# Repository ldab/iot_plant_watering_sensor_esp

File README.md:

# iot_plant_watering_sensor_esp32
Connected, IoT, WiFi capacitance plant watering sensor based on ESP32

 ## TODO

- [ ] Better battery polarity indication and reverse polarity protection;
- [ ] Fix R16 - R19 Silk
- [ ] R15 is leaking 200uA
- [ ] Check if `esp_light_sleep_start()` improves current vs `delay(x)`
- [ ] Inspect connection time if BSSID is saved vs Saving time
- [ ] FOTA
- [ ] Error reporting and callbacks, i.e FFAT, ADC read, etc..

## VOID

"Lorem ipsum dolor sit amet, consectetur adipiscing elit, sed do eiusmod tempor incididunt ut labore et dolore magna aliqua. Ut enim ad minim veniam, quis nostrud exercitation ullamco laboris nisi ut aliquip ex ea commodo consequat. Duis aute irure dolor in reprehenderit in voluptate velit esse cillum dolore eu fugiat nulla pariatur. Excepteur sint occaecat cupidatat non proident, sunt in culpa qui officia deserunt mollit anim id est laborum."

## Working modes and button

* The device will check the moisture 2x a day, at 8am and 6pm;
* On Sundays it will connect to the internet and check time, etc;
* Insert the battery **WATCH THE POLAITY**;
* Press and hold the `config` button;
  * keep it pressed, it will connect to the internet, get the time and date and calibrate the sensor;
  * if everything goes well, it buzzes like this [link for audio]()
* If the battery voltage is lower than 2V, an `email` will be sent and it buzzes like this [link for audio](./ringtones/urgent.mid)
* If the soil is drier than the setpoint, an `email` will be sent and it buzzes like this [link for audio]()
* If a new level of alarm is nedded, press and hold the config button until a buzz like this [link for audio]() is heard;

## Component selection and Capacitive probe

* We need the most range on the voltage across the probe as possible, considering

**`Vc = 3 * (1 - e(-t / (R * C)))`**

* Varying R from 100 to 15000 Ω @ 1MHz:

[Wolfram Alpha - R Graph](https://www.wolframalpha.com/input/?i=plot+3+*+%281+-+e%5E%28-500*10%5E-9%2F%28R*50*10%5E-12%29%29%29+-+3+*+%281+-+e%5E%28-500*10%5E-9%2F%28R*200*10%5E-12%29%29%29%2C+R%3D+100+to+15000)

* From the graph below we go with 5KΩ, the capacitance of the probe varies from 50pF to 200pF:

[Wolfram Alpha - C Graph](https://www.wolframalpha.com/input/?i=plot+3+*+%281+-+e%5E%28-500*10%5E-9%2F%285000*C%29%29%29%2C+C%3D50*10%5E-12+to+200*10%5E-12)

* With a voltage range of 2.6 to 1.2 **~1.4V**.

## Capacitive sensor measurement

* When in the air, the sensor measures ~2.67V @ 1666(adc)

.BMP)

* And below 1000 (adc) ~1.8V when wet soil/water

.BMP)

## PSEUDO-CODE

```
main()
{ 
  turn radio OFF;
  config pins;

  read RTC();

  if( dateIsNotSet )    // probably first time
  {
    beep 2x;
    connect to the internet;
    set date;
    config RTC;
  }

  read moisture;

  if( alarmIsNotActive ) // wake from button
  {
    beep 5x;
    set new moisture level;
    clear alarm flag;    // aka sleep
  }
  else
  {
    if( moisture < threshould)
    {
      connect to the internet;
      send email/MQTT;
      turn radio OFF;

      while( times )
      {
        chrip
      }

      wake 
      clear alarm flag;    // aka sleep
    }
    else
    {
      clear alarm flag;    // aka sleep
    }
  }

  printf should never get here
} 
```

## Power Profile

* The DHCP negotiation and IP assignment can take a long time depending on the router, the below example is from a fairly long avg 90mA@2.8V for 3 s -> Includes ADC reading and MQTT publish

* When not connecting to WiFi, it is a lot faster:

* And during sleep 6uA@2.8V maninly due to the battery ADC (VCC/1MOhm =~ 3uA) and Boost disabled, ~1uA

* Primary battery CR-2 drops a bit during active, 280mv:

## Calibrating ADC for ESP32

* ADC on ESP32 has been reported being innacurate, therefore one can use ```adc2_vref_to_gpio( GPIO_NUM_25 );``` to route `Vref` to `GPIO_NUM_25` that can be measured over `ESP32 pin 10` in order to calibrate during ADC measurement.
* Calling for `esp_adc_cal_characterize(ADC_UNIT_1, ADC_ATTEN_DB_6, ADC_WIDTH_BIT_11, Vref, adc_chars);`

https://docs.espressif.com/projects/esp-idf/zh_CN/latest/esp32/api-reference/peripherals/adc.html

## FFat and time

```
  [641] IP address: 192.168.0.22
  Contacting Time Server
  [854] Now is : 2020-11-27T16:37:33
  Writing file: /hello.txt
  File written
  [1030] DONE writing, took: 176ms
  Reading file: /hello.txt
  Read from file: 2020-11-27T16:37:33
  [1093] DONE reading, took: 5ms
```

## Schematic

## PCB

## Enclosure

## Known Limitations

* 

## Credits

Github Shields and Badges created with [Shields.io](https://github.com/badges/shields/)

Inspired by [chirp! - the plant watering alarm](https://wemakethings.net/chirp/)

ESP32 Pin definition and overview https://randomnerdtutorials.com/esp32-pinout-reference-gpios/

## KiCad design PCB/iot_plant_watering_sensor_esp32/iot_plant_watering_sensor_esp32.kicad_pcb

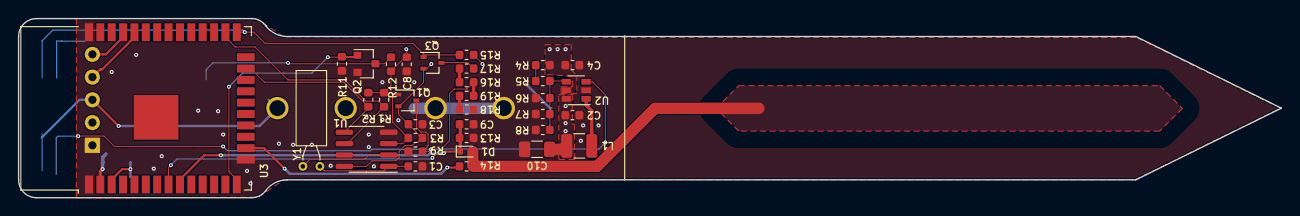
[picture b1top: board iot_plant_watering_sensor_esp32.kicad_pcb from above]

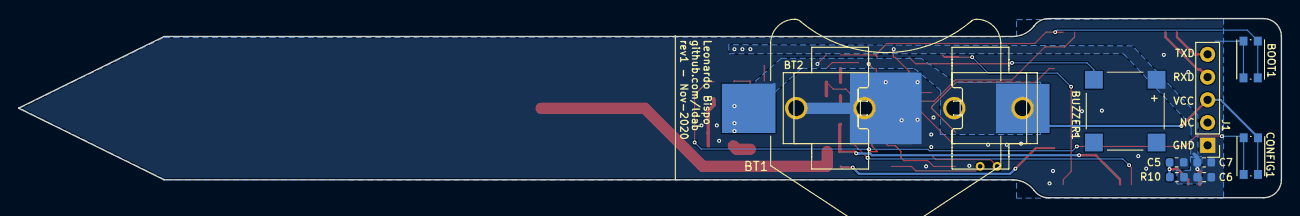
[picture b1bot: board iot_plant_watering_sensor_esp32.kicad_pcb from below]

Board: 2 copper layers, 141.0 x 20.0 mm, 44 parts (10 on the bottom side), 25 nets.

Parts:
BOOT1: SW_Push_KMR2; SW_Push_1P1T_NO_CK_KMR2
BT1: LIR2450; BatteryHolder_Keystone_3008_1x2450
BT2: CR2; 2915_CR2
BUZZER1: FUET-8530H-3.6V; PUIAudio_SMT_0825_S_4_R
C1: 25p; C_0603_1608Metric
C2, C4, C7: 10u; C_0603_1608Metric
C3, C5, C6: 100n; C_0603_1608Metric
C8, C9: 1u; C_0603_1608Metric
C10: 100u; C_1206_3216Metric
CONFIG1: SW_Push_KMR2; SW_Push_1P1T_NO_CK_KMR2
D1: RB751S40T1G; D_SOD-523
J1: Conn_01x05; PinHeader_1x05_P2.54mm_Snuggly
L1: 4.7u; L_1210_3225Metric
Q1, Q3: BSS84W-7-F; SOT-323_SC-70
Q2: 2N7002P,215; SOT-23
R1, R2, R3, R9, R10, R11, R14, R15: 10K; R_0603_1608Metric
R4, R5, R6, R7, R8, R13, R16, R17, R18, R19: 510K; R_0603_1608Metric
R12: 1K; R_0603_1608Metric
U1: PCF8563T; SOIC-8_3.9x4.9mm_P1.27mm
U2: FP6714; SOT-23-6
U3: ESP32-WROOM-32
Y1: 32.768 kHz; Crystal_C38-LF_D3.0mm_L8.0mm_Horizontal

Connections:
+3V3: BUZZER1.1, C4.1, C6.1, C7.1, C8.1, R1.2, R2.2, R4.1, R10.2, R12.1, U2.5, U3.2
+BATT: BT1.1, BT2.1, C2.1, C3.1, C10.1, CONFIG1.2, J1.3, L1.1, Q1.2, Q3.2, R3.2, R15.2, U1.8, U2.6
/C_SENSOR+: D1.2, R14.2
BATT_ADC: R17.2, R18.1, U3.8
BOOT: BOOT1.2, Q3.1, R15.1, U3.25
BUZZER: Q2.1, R11.2, U3.14
C_SENSE: C9.1, D1.1, R13.1, U3.9
FB: R5.2, R6.1, R7.1, R8.1, U2.4
GND: BOOT1.1, BT1.2, BT2.2, C1.2, C2.2, C3.2, C4.2, C5.2, C6.2, C7.2, C8.2, C9.2, C10.2, J1.1, Q2.2, R6.2, R7.2, R8.2, R9.1, R11.1, R13.2, R19.2, U1.4, U2.2, U3.1, U3.15, U3.38
LDO_EN: CONFIG1.1, Q1.3, R9.2, U2.3
unnamed: BUZZER1.2, Q2.3, R12.2
unnamed: C1.1, U1.1, Y1.1
unnamed: C5.1, R10.1, U3.3
unnamed: L1.2, U2.1
unnamed: Q1.1, R3.1, U1.3
unnamed: Q3.3, R16.1
unnamed: R4.2, R5.1
unnamed: R16.2, R17.1
unnamed: R18.2, R19.1
unnamed: U1.2, Y1.2
PWM: R14.1, U3.16
RXD: J1.4, U3.34
SCL: R1.1, U1.6, U3.26
SDA: R2.1, U1.5, U3.23
TXD: J1.5, U3.35

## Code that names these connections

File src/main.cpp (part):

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
#define VREF_CALIB 1098  // #define CALIBRATE and measure Vref

#define C_SENSE A5   // GPIO33 - IO33/ADC1_CH5
#define BATT_ADC A4  // GPIO32 - IO32/ADC1_CH4
#define BATT_EN A11  // GPIO0
#define PWM A14      // GPIO13
#define BUZZER A15   // GPIO12
#define SDA_PIN A13  // GPIO15
#define SCL_PIN A10  // GPIO04

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
  ledcAttachPin(PWM, PWM_CHANNEL);

  ledcAttachPin(BUZZER, BUZZER_CHANNEL);

  adc1_config_width(ADC_WIDTH_BIT_11);  // Reduce ADC resolution due to reported
                                        // noise on 12 bits
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
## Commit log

2020-11-21 initial comit
2020-11-21 fix travis
2020-11-21 build badge
2020-11-22 schematic and PIN definition
2020-11-22 RTC and pinInit
2020-11-25 schematic pre-release
2020-11-25 finished schematic
2020-11-25 pcb release
2020-11-25 pre-release no post http
2020-11-27 MQTT topics
2020-11-28 enclosure gif
2020-11-28 fix PWM out and FFAT
2020-11-29 components calc
2020-12-03 untested RTTTL - Google format
2020-12-03 test song
2020-12-08 minor
2020-12-18 5uA sleep current -> dev drop
2020-12-18 platformio
2020-12-22 batt ADC fix
2020-12-22 fix first config time
2020-12-22 sanity loop
2020-12-22 3D files
2020-12-22 CR-2 batt voltage meas
2020-12-23 clean debug
2020-12-28 fix PWM call, 10 bits stuff and def
2020-12-28 clean DBG
2020-12-28 working, release test
2020-12-28 osciloscope pics
2021-01-11 WiFi and MQTT error report
2021-01-11 new partition, allow OTA
2021-01-11 disable brownout detector
2021-01-11 new variable and tidy comments
2021-01-11 250ms delay for cap ADC
2021-01-11 Wake 2x a day, 8am and 18
2021-01-11 report measurement always
2021-01-11 send error_TODO
2021-01-11 OSC pics
2021-01-11 Async mqtt (#1)
    * initial comit
    * schematic and PIN definition
    * RTC and pinInit
    * pcb release
    * Merge branch 'dev' of https://github.com/ldab/iot_plant_watering_sensor_esp32 into dev
    * NTP
2021-01-11 broke
2021-01-11 OTA untested
2021-01-11 power graph
2021-01-12 fix RTTL lib, size and atoi
2021-01-12 add songs
2021-01-12 Ffat partition breaks
2021-01-12 esp32_exception_decoder
2021-01-12 format

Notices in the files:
README.md:
License: MIT
